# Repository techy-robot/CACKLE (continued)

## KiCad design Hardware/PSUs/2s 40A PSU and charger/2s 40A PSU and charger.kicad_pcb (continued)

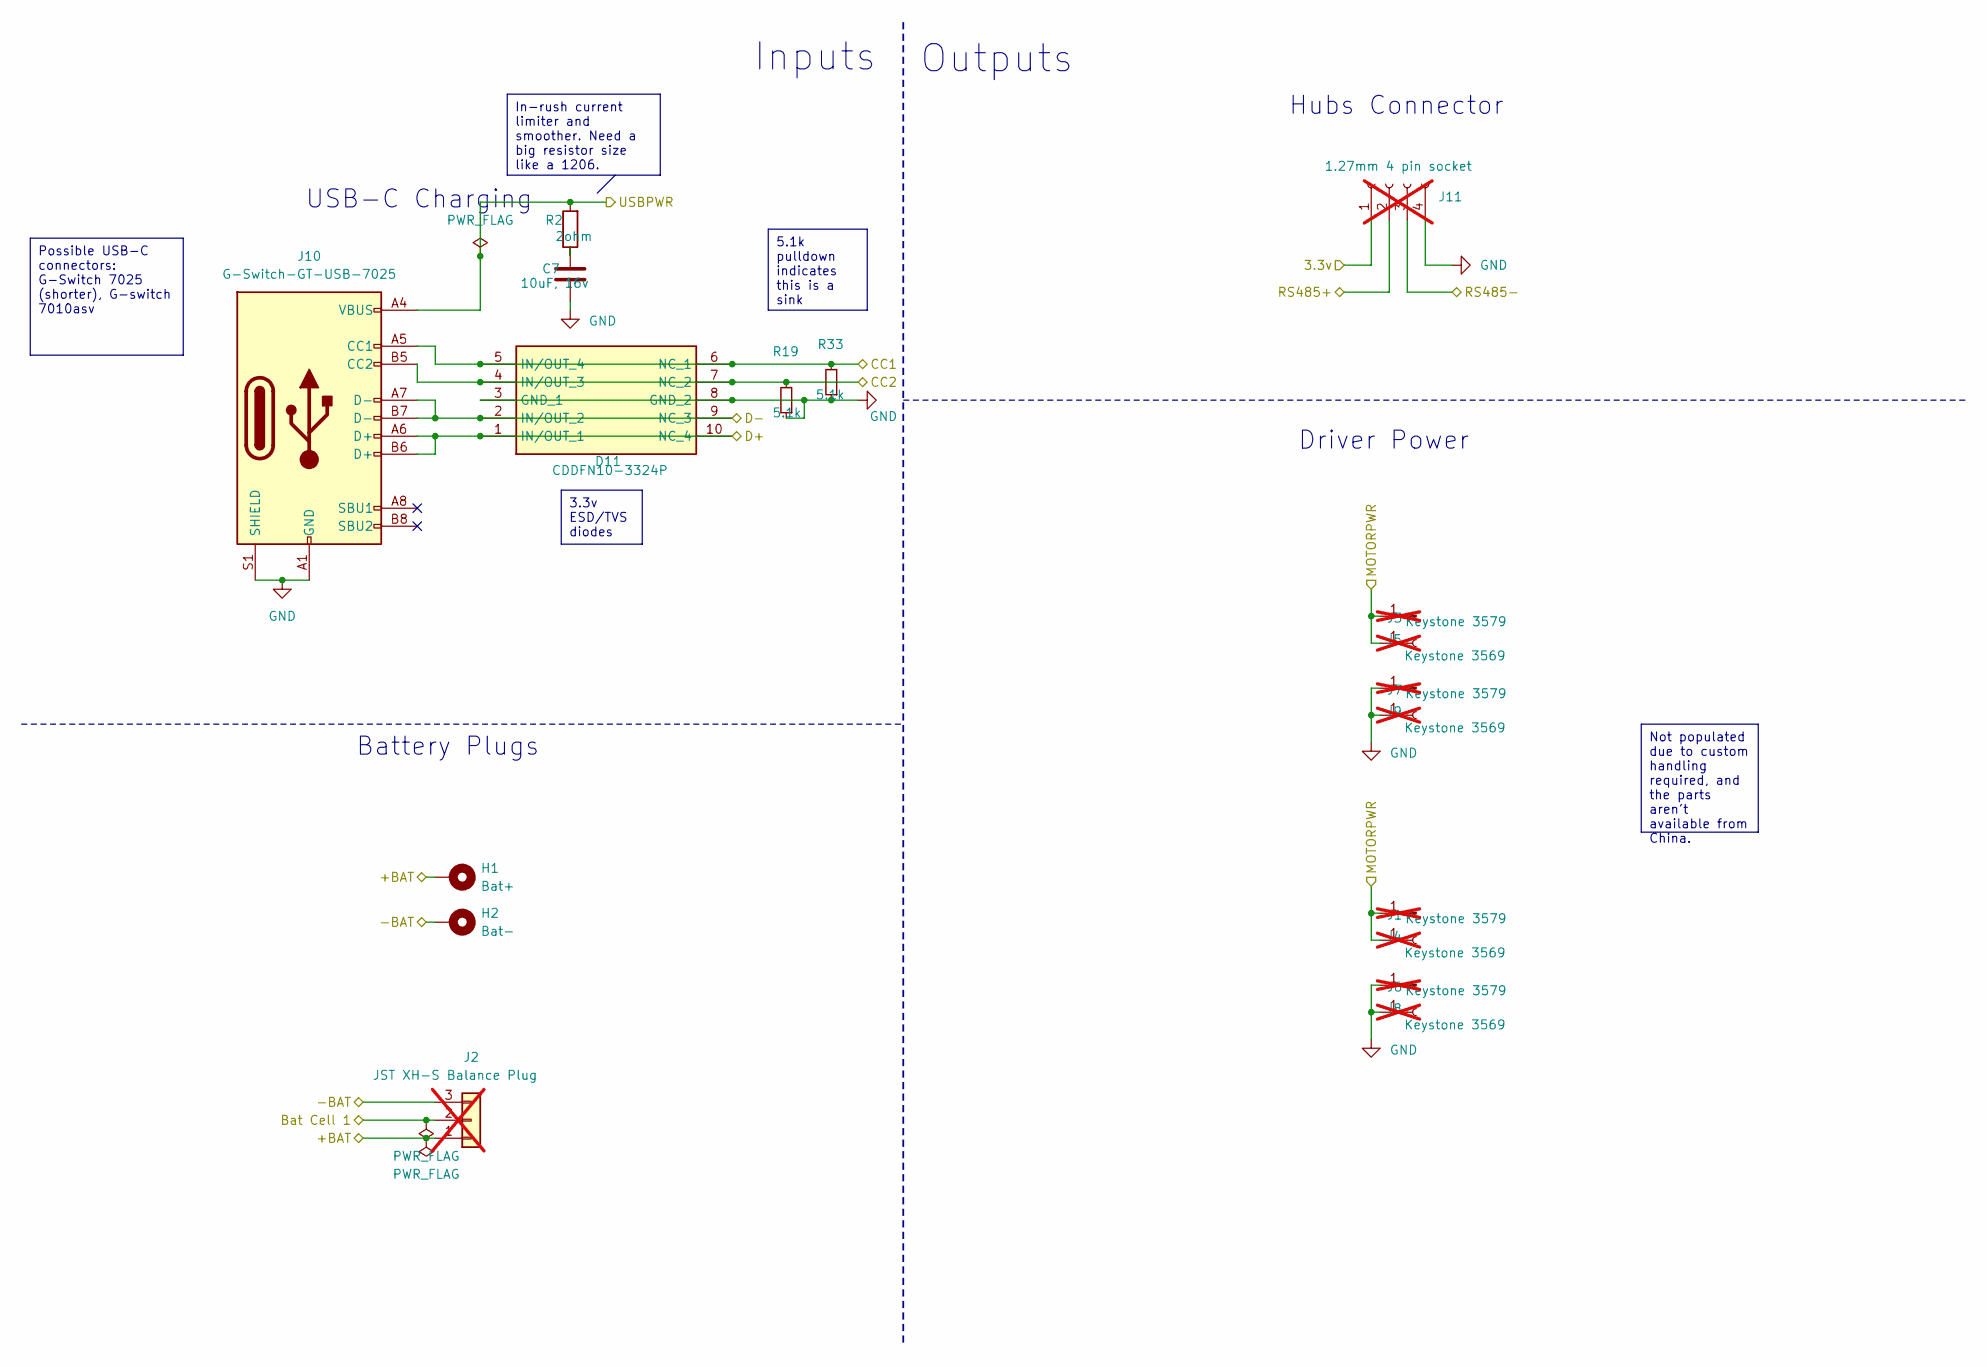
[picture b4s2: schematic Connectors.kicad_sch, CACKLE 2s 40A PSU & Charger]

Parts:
C7: 10uF, 16v; C_0805_2012Metric; LCSC C15850
D11: CDDFN10-3324P; CDDFN103324P; Mouser Part Number 652-CDDFN10-3324P
H1: Bat+; MountingHole_2.2mm_M2_Pad_Via
H2: Bat-; MountingHole_2.2mm_M2_Pad_Via
J1, J3, J6, J7: Keystone 3579; Keystone_3579; not fitted
J2: JST XH-S Balance Plug; JST_XH_S3B-XH-A_1x03_P2.50mm_Horizontal; LCSC C161860; not fitted
J4, J5, J8, J9: Keystone 3569; Keystone_3569_half; not fitted
J10: G-Switch-GT-USB-7025; USB_C_G-Switch_GT-USB-7025-JLCPCBv; LCSC C963213
J11: 1.27mm 4 pin socket; PinSocket_1x04_P1.27mm_Vertical; not fitted
R2: 2ohm; R_0805_2012Metric; LCSC C17521
R19, R33: 5.1k; R_0402_1005Metric; LCSC C25905

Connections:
/Battery Balancer/+BAT: H1.1, J2.1; also elsewhere on the board
/Battery Balancer/-BAT: H2.1, J2.3; also elsewhere on the board
/Battery Balancer/Bat Cell 1: J2.2; also elsewhere on the board
/Battery Charger/IN: J10.A4 (VBUS), J10.A9 (VBUS), J10.B4 (VBUS), J10.B9 (VBUS), R2.2; also elsewhere on the board
/Battery Charger/MOTORPWR: J1.1, J3.1, J4.1, J5.1; also elsewhere on the board
/Connectors/3.3v: J11.1; also elsewhere on the board
/Connectors/CC1: D11.5 (IN/OUT_4), D11.6 (NC_1), J10.A5 (CC1), R33.2; also elsewhere on the board
/Connectors/CC2: D11.4 (IN/OUT_3), D11.7 (NC_2), J10.B5 (CC2), R19.2; also elsewhere on the board
/Connectors/D+: D11.1 (IN/OUT_1), D11.10 (NC_4), J10.A6 (D+), J10.B6 (D+); also elsewhere on the board
/Connectors/D-: D11.2 (IN/OUT_2), D11.9 (NC_3), J10.A7 (D-), J10.B7 (D-); also elsewhere on the board
/Connectors/RS485+: J11.2; also elsewhere on the board
/Connectors/RS485-: J11.3; also elsewhere on the board
GND: C7.2, D11.3 (GND_1), D11.8 (GND_2), J6.1, J7.1, J8.1, J9.1, J10.A1 (GND), J10.A12 (GND), J10.B1 (GND), J10.B12 (GND), J10.GND, J10.S1 (SHIELD), J11.4, R19.1, R33.1; also elsewhere on the board
unnamed: C7.1, R2.1

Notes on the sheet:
In-rush current limiter and smoother. Need a big resistor size like a 1206.
5.1k pulldown indicates this is a sink
Possible USB-C connectors: G-Switch 7025 (shorter), G-switch 7010asv
3.3v ESD/TVS diodes
Not populated due to custom handling required, and the parts aren't available from China.
Outputs
USB-C Charging
Inputs
Driver Power
Hubs Connector
Battery Plugs

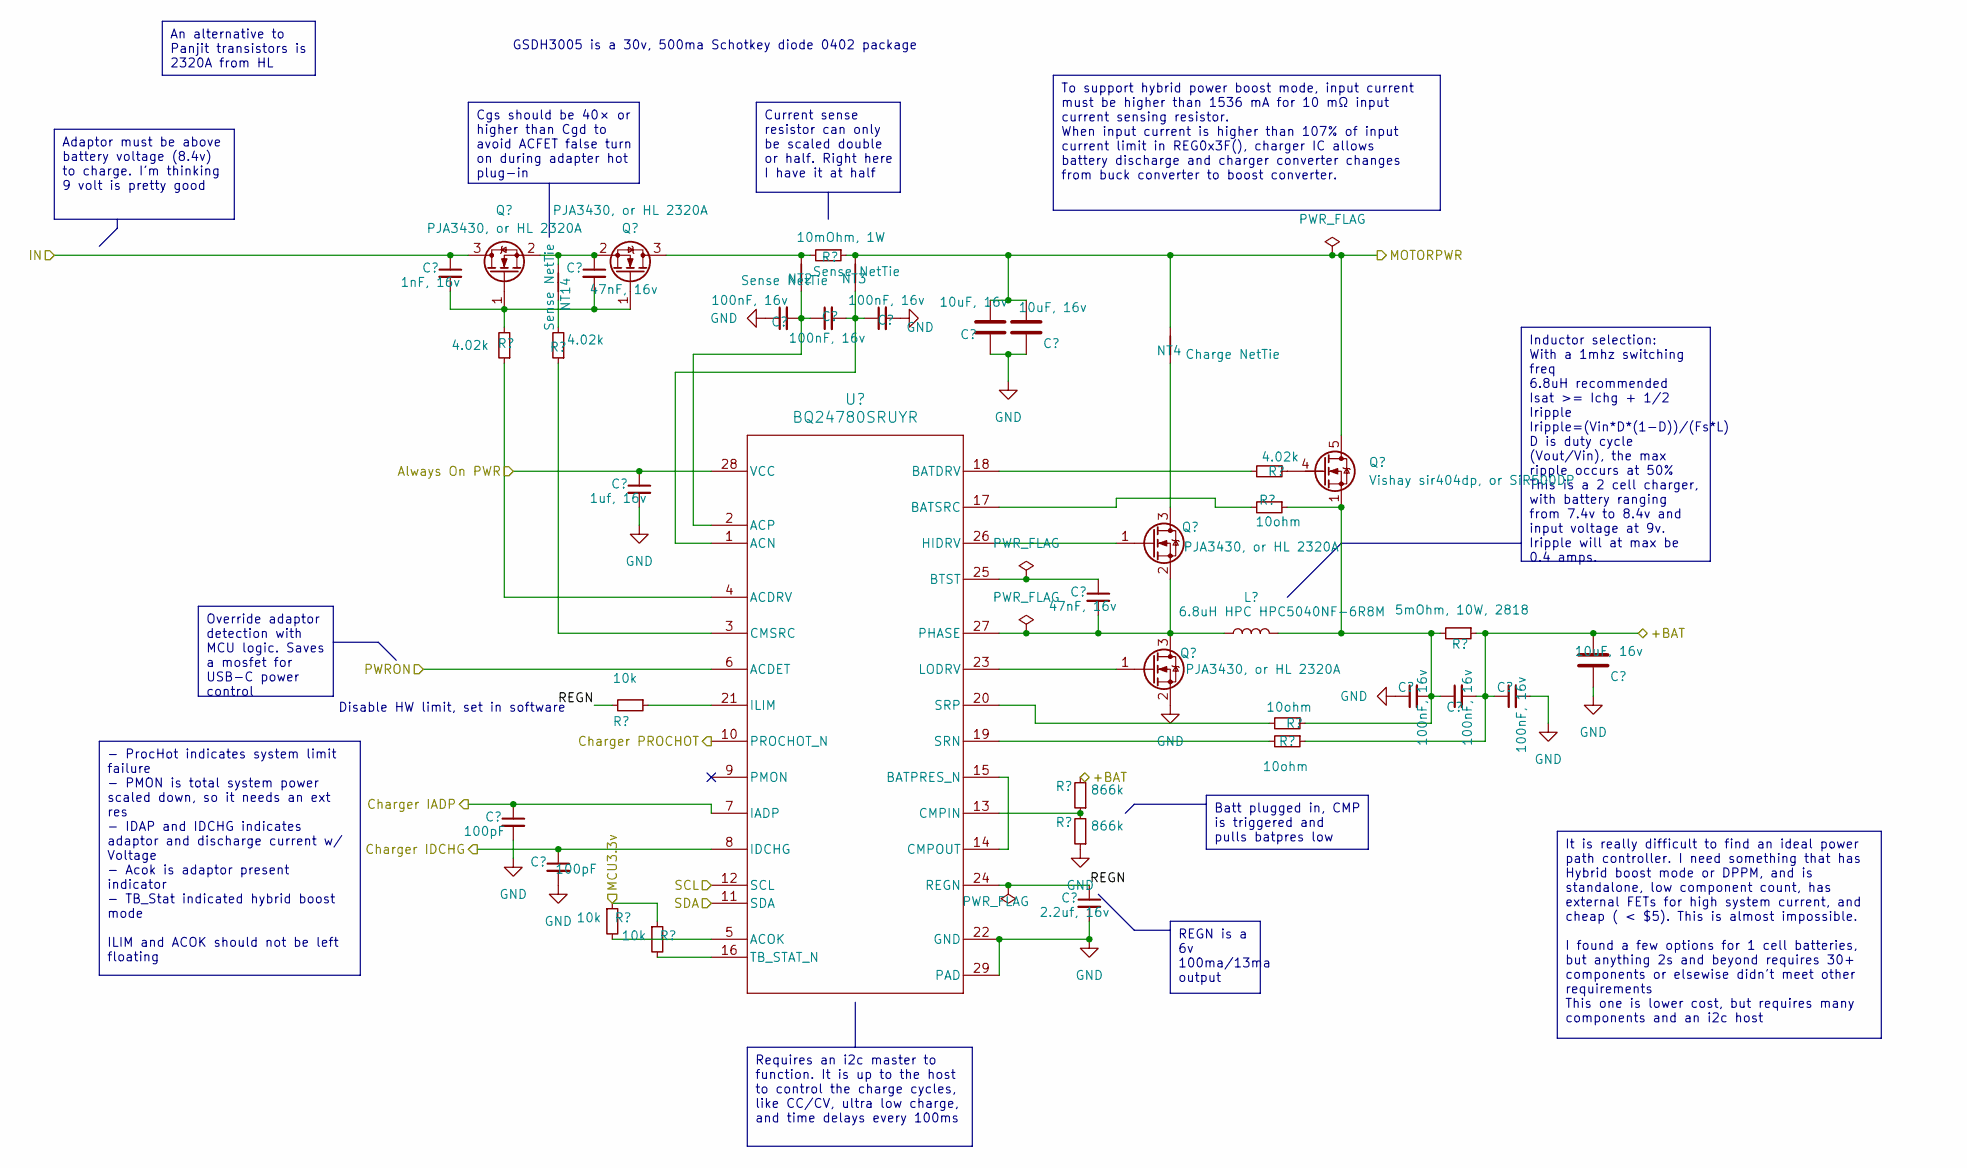
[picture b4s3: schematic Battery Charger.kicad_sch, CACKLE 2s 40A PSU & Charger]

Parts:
C5: 1nF, 16v; C_0402_1005Metric
C6, C17: 47nF, 16v; C_0603_1608Metric
C9, C10, C11, C21, C22, C23: 100nF, 16v; C_0402_1005Metric
C12, C14, C20: 10uF, 16v; C_0805_2012Metric
C15: 1uf, 16v; C_0402_1005Metric
C24: 2.2uf, 16v; C_0603_1608Metric
C29, C30: 100pF; C_0402_1005Metric
L2: 6.8uH HPC HPC5040NF-6R8M; L_Bourns_SDR0604
NT2, NT3, NT14: Sense NetTie; NetTie-2_SMD_Pad0.2mm
NT4: Charge NetTie; NetTie-2_SMD_Pad0.8mm
Q1, Q2, Q4, Q5: PJA3430, or HL 2320A; SC-59
Q3: Vishay sir404dp, or SiR500DP; PQFN-8-EP_6x5mm_P1.27mm_Generic; LCSC C3289487
R1: 10mOhm, 1W; R_1206_3216Metric
R7, R8, R10: 4.02k; R_0402_1005Metric
R12, R21, R22: 10ohm; R_0402_1005Metric
R18: 5mOhm, 10W, 2818; R_Vishay_2818
R20, R23, R24: 10k; R_0402_1005Metric
R30, R31: 866k; R_0402_1005Metric
U3: BQ24780SRUYR; RUY0028A

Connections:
/Battery Balancer/+BAT: C20.2, C22.2, C23.1, R18.1, R22.1, R30.2; also elsewhere on the board
/Battery Charger/Always On PWR: C15.1, U3.28 (VCC); also elsewhere on the board
/Battery Charger/Charger IADP: C29.1, U3.7 (IADP); also elsewhere on the board
/Battery Charger/Charger IDCHG: C30.1, U3.8 (IDCHG); also elsewhere on the board
/Battery Charger/Charger PROCHOT: U3.10 (PROCHOT_N); also elsewhere on the board
/Battery Charger/IN: C5.1, Q1.3 (D); also elsewhere on the board
/Battery Charger/MCU3.3v: R23.1, R24.1; also elsewhere on the board
/Battery Charger/MOTORPWR: C12.2, C14.2, NT3.2, NT4.2, Q3.5 (D), Q3.6 (D), Q3.7 (D), Q3.8 (D), R1.1; also elsewhere on the board
/Battery Charger/PWRON: U3.6 (ACDET); also elsewhere on the board
/Battery Charger/REGN: C24.1, R20.2, U3.24 (REGN)
/SCL: U3.12 (SCL); also elsewhere on the board
/SDA: U3.11 (SDA); also elsewhere on the board
GND: C9.1, C11.2, C12.1, C14.1, C15.2, C20.1, C21.1, C23.2, C24.2, C29.2, C30.2, Q5.2 (S), R31.1, U3.22 (GND), U3.29 (PAD); also elsewhere on the board
unnamed: C21.2, C22.1, L2.2, Q3.1 (S), Q3.2 (S), Q3.3 (S), R12.1, R18.2, R21.1
unnamed: NT14.1, R7.2
unnamed: C5.2, C6.2, Q1.1 (G), Q2.1 (G), R8.2
unnamed: C6.1, NT14.2, Q1.2 (S), Q2.2 (S)
unnamed: NT2.2, Q2.3 (D), R1.2
unnamed: Q3.4 (G), R10.1
unnamed: NT4.1, Q4.3 (D)
unnamed: Q4.1 (G), U3.26 (HIDRV)
unnamed: C17.2, L2.1, Q4.2 (S), Q5.3 (D), U3.27 (PHASE)
unnamed: Q5.1 (G), U3.23 (LODRV)
unnamed: R8.1, U3.4 (ACDRV)
unnamed: C10.2, C11.1, NT3.1, U3.1 (ACN)
unnamed: R23.2, U3.5 (ACOK)
unnamed: C9.2, C10.1, NT2.1, U3.2 (ACP)
unnamed: R10.2, U3.18 (BATDRV)
unnamed: U3.14 (CMPOUT), U3.15 (BATPRES_N)
unnamed: R12.2, U3.17 (BATSRC)
unnamed: C17.1, U3.25 (BTST)
unnamed: R30.1, R31.2, U3.13 (CMPIN)
unnamed: R7.1, U3.3 (CMSRC)
unnamed: R20.1, U3.21 (ILIM)
unnamed: R22.2, U3.19 (SRN)
unnamed: R21.2, U3.20 (SRP)
unnamed: R24.2, U3.16 (TB_STAT_N)

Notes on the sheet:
To support hybrid power boost mode, input current must be higher than 1536 mA for 10 mΩ input current sensing resistor. When input current is higher than 107% of input current limit in REG0x3F(), charger IC allows battery discharge and charger converter changes from buck converter to boost converte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
Batt plugged in, CMP is triggered and pulls batpres low
Inductor selection: With a 1mhz switching freq 6.8uH recommended Isat >= Ichg + 1/2 Iripple Iripple=(Vin*D*(1-D))/(Fs*L) D is duty cycle (Vout/Vin), the max ripple occurs at 50% This is a 2 cell charger, with battery ranging from 7.4v to 8.4v and input voltage at 9v. Iripple will at max be 0.4 amps.
It is really difficult to find an ideal power path controller. I need something that has Hybrid boost mode or DPPM, and is standalone, low component count, has external FETs for high system current, and cheap ( < $5). This is almost impossible. I found a few options for 1 cell batteries, but anythi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
Requires an i2c master to function. It is up to the host to control the charge cycles, like CC/CV, ultra low charge, and time delays every 100ms
Cgs should be 40× or higher than Cgd to avoid ACFET false turn on during adapter hot plug-in
Current sense resistor can only be scaled double or half. Right here I have it at half
Override adaptor detection with MCU logic. Saves a mosfet for USB-C power control
Adaptor must be above battery voltage (8.4v) to charge. I'm thinking 9 volt is pretty good
REGN is a 6v 100ma/13ma output
An alternative to Panjit transistors is 2320A from HL
- ProcHot indicates system limit failure - PMON is total system power scaled down, so it needs an ext res - IDAP and IDCHG indicates adaptor and discharge current w/ Voltage - Acok is adaptor present indicator - TB_Stat indicated hybrid boost mode ILIM and ACOK should not be left floating
GSDH3005 is a 30v, 500ma Schotkey diode 0402 package
Disable HW limit, set in software

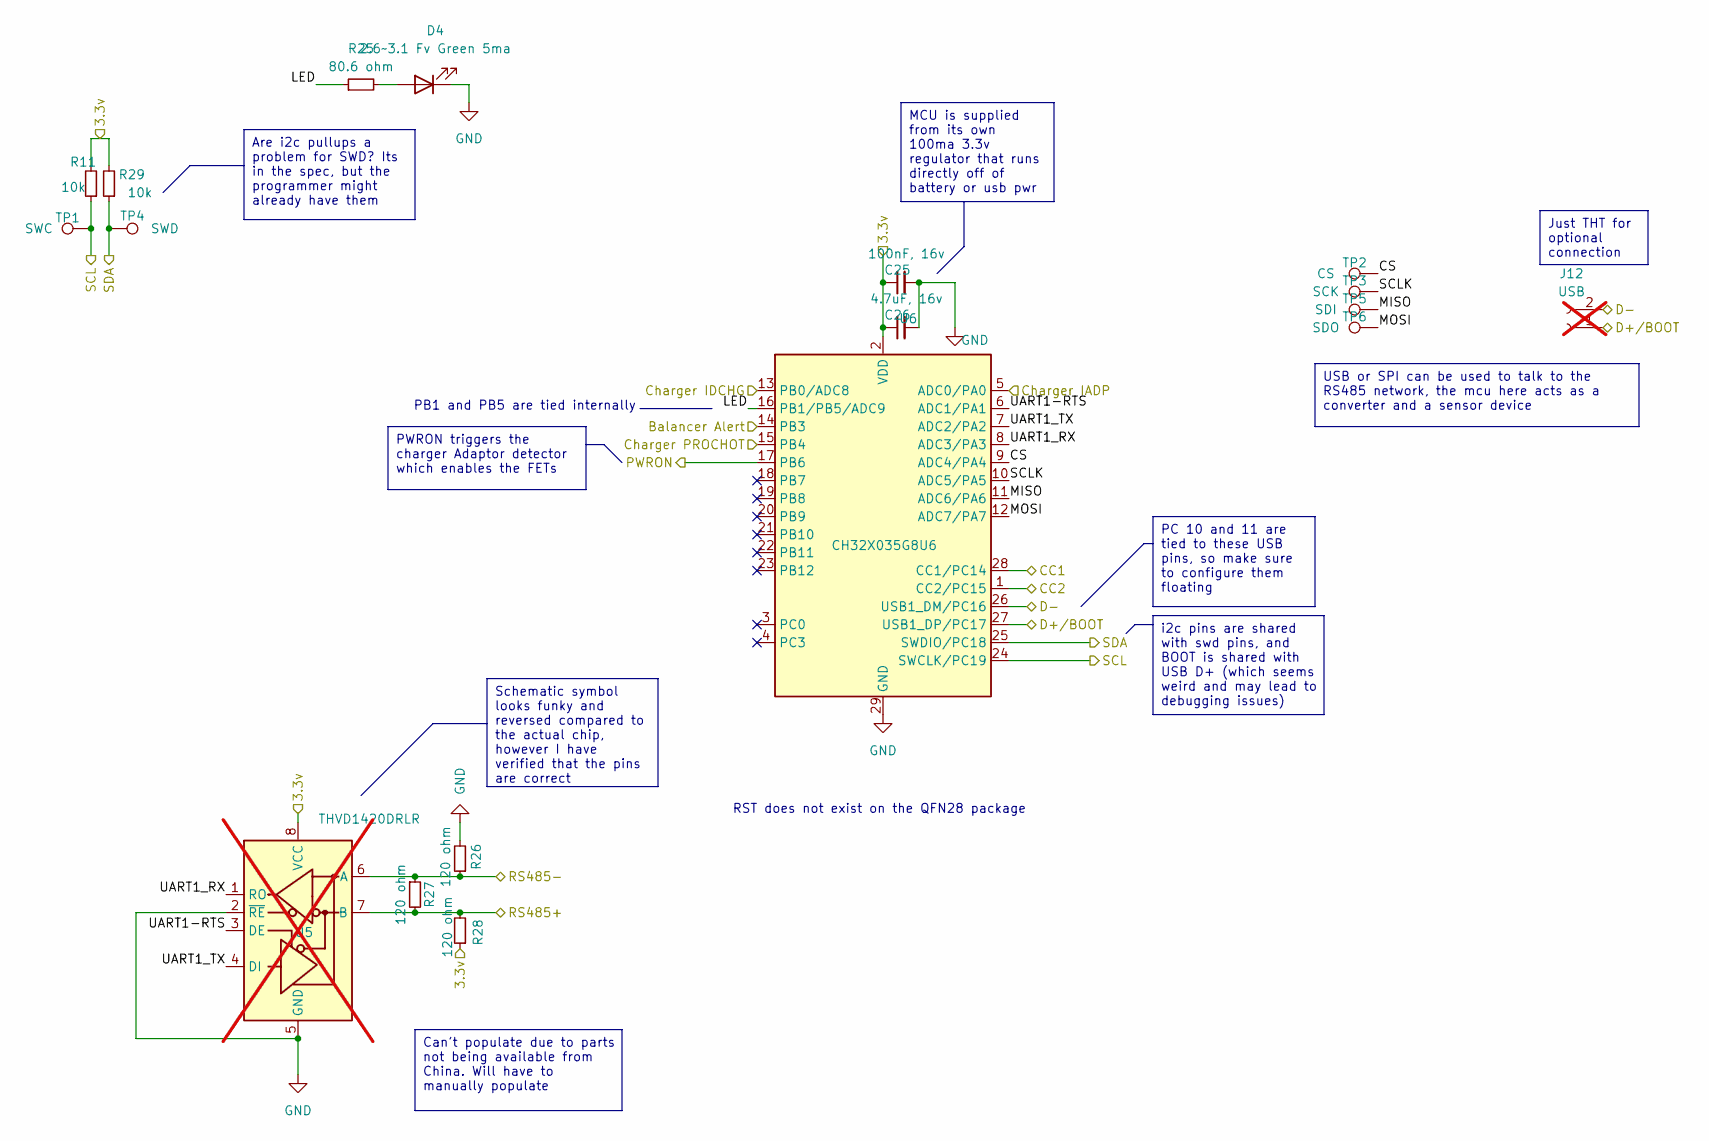
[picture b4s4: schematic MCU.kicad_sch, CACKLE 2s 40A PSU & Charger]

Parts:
C25: 100nF, 16v; C_0402_1005Metric; LCSC C1525
C26: 4.7uF, 16v; C_0603_1608Metric; LCSC C19666
D4: 2.6~3.1 Fv Green 5ma; LED_0603_1608Metric_Pad1.05x0.95mm_HandSolder; LCSC C3028858
J12: USB; PinHeader_1x02_P1.27mm_Vertical; not fitted
R11, R29: 10k; R_0402_1005Metric; LCSC C25744
R25: 80.6 ohm; R_0402_1005Metric; LCSC C185392
R26, R27, R28: 120 ohm; R_0402_1005Metric; LCSC C25079
TP1: SWC; TestPoint_Pad_D1.0mm
TP2: CS; TestPoint_Pad_D1.0mm
TP3: SCK; TestPoint_Pad_D1.0mm
TP4: SWD; TestPoint_Pad_D1.0mm
TP5: SDI; TestPoint_Pad_D1.0mm
TP6: SDO; TestPoint_Pad_D1.0mm
U5: THVD1420DRLR; SOT-583-8; not fitted
U6: CH32X035G8U6; QFN-28-1EP_4x4mm_P0.4mm_EP2.8x2.8mm; LCSC C7437027

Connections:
/Battery Balancer/Balancer Alert: U6.14 (PB3); also elsewhere on the board
/Battery Charger/Charger IADP: U6.5 (ADC0/PA0); also elsewhere on the board
/Battery Charger/Charger IDCHG: U6.13 (PB0/ADC8); also elsewhere on the board
/Battery Charger/Charger PROCHOT: U6.15 (PB4); also elsewhere on the board
/Battery Charger/MCU3.3v: C25.1, C26.1, R11.2, R28.1, R29.2, U5.8 (VCC), U6.2 (VDD); also elsewhere on the board
/Battery Charger/PWRON: U6.17 (PB6); also elsewhere on the board
/Connectors/CC1: U6.28 (CC1/PC14); also elsewhere on the board
/Connectors/CC2: U6.1 (CC2/PC15); also elsewhere on the board
/Connectors/D+: J12.1, U6.27 (USB1_DP/PC17); also elsewhere on the board
/Connectors/D-: J12.2, U6.26 (USB1_DM/PC16); also elsewhere on the board
/Connectors/RS485+: R27.2, R28.2, U5.7 (B); also elsewhere on the board
/Connectors/RS485-: R26.1, R27.1, U5.6 (A); also elsewhere on the board
/MCU/CS: TP2.1, U6.9 (ADC4/PA4)
/MCU/LED: R25.1, U6.16 (PB1/PB5/ADC9)
/MCU/MISO: TP5.1, U6.11 (ADC6/PA6)
/MCU/MOSI: TP6.1, U6.12 (ADC7/PA7)
/MCU/SCLK: TP3.1, U6.10 (ADC5/PA5)
/MCU/UART1-RTS: U5.3 (DE), U6.6 (ADC1/PA1)
/MCU/UART1_RX: U5.1 (RO), U6.8 (ADC3/PA3)
/MCU/UART1_TX: U5.4 (DI), U6.7 (ADC2/PA2)
/SCL: R11.1, TP1.1, U6.24 (SWCLK/PC19); also elsewhere on the board
/SDA: R29.1, TP4.1, U6.25 (SWDIO/PC18); also elsewhere on the board
GND: C25.2, C26.2, D4.1 (K), R26.2, U5.2 (~RE), U5.5 (GND), U6.29 (GND); also elsewhere on the board
unnamed: D4.2 (A), R25.2

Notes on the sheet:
i2c pins are shared with swd pins, and BOOT is shared with USB D+ (which seems weird and may lead to debugging issues)
MCU is supplied from its own 100ma 3.3v regulator that runs directly off of battery or usb pwr
USB or SPI can be used to talk to the RS485 network, the mcu here acts as a converter and a sensor device
Just THT for optional connection
PC 10 and 11 are tied to these USB pins, so make sure to configure them floating
PWRON triggers the charger Adaptor detector which enables the FETs
Can't populate due to parts not being available from China. Will have to manually populate
Schematic symbol looks funky and reversed compared to the actual chip, however I have verified that the pins are correct
Are i2c pullups a problem for SWD? Its in the spec, but the programmer might already have them
RST does not exist on the QFN28 package
PB1 and PB5 are tied internally

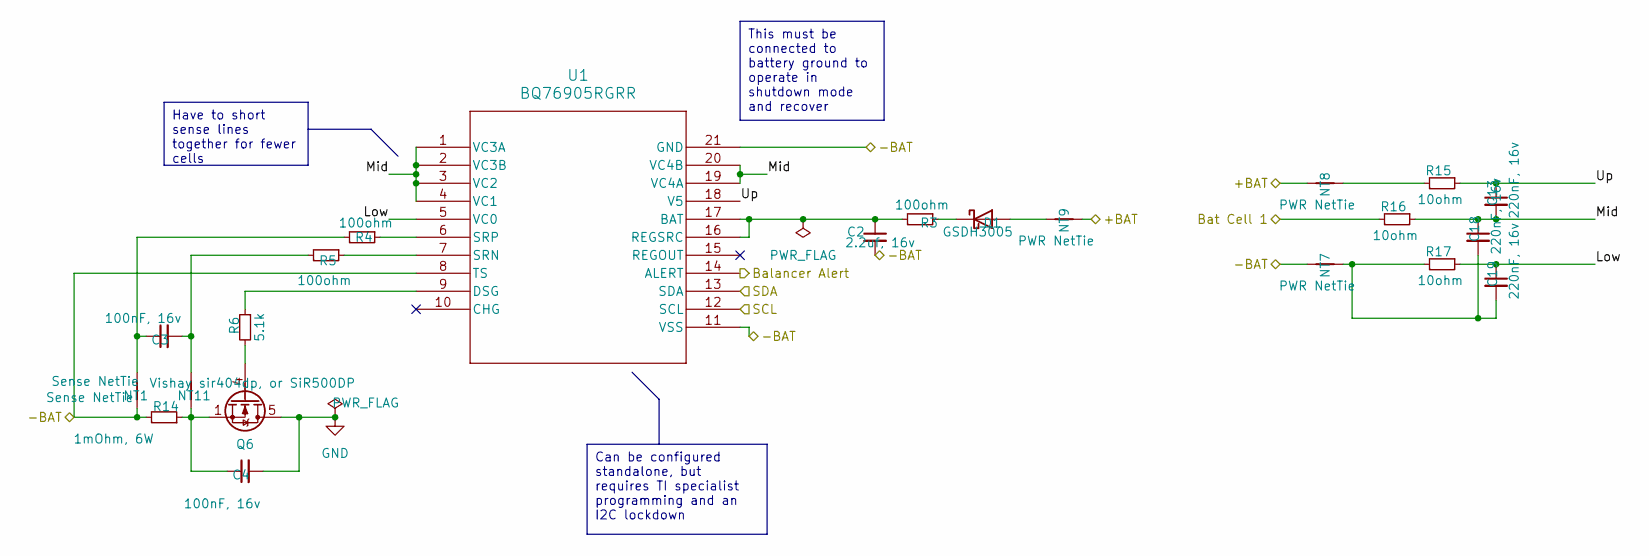
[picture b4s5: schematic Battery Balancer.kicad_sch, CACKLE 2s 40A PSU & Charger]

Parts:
C2: 2.2uf, 16v; C_0603_1608Metric; LCSC C23630
C3, C4: 100nF, 16v; C_0402_1005Metric; LCSC C1525
C13, C18, C19: 220nF, 16v; C_0402_1005Metric; LCSC C16772
D1: GSDH3005; D_0402_1005Metric; LCSC C2837790
NT1, NT11: Sense NetTie; NetTie-2_SMD_Pad0.2mm
NT7, NT8, NT9: PWR NetTie; NetTie-2_SMD_Pad0.28mm
Q6: Vishay sir404dp, or SiR500DP; PQFN-8-EP_6x5mm_P1.27mm_Generic; LCSC C3289487
R3, R4, R5: 100ohm; R_0402_1005Metric; LCSC C25076
R6: 5.1k; R_0402_1005Metric; LCSC C25905
R14: 1mOhm, 6W; R_2512_6332Metric_6W; LCSC C19270875
R15, R16, R17: 10ohm; R_0402_1005Metric; LCSC C25077
U1: BQ76905RGRR; VQFN20_RGR_TEX; LCSC C22394458

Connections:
/Battery Balancer/+BAT: NT8.2, NT9.1; also elsewhere on the board
/Battery Balancer/-BAT: C2.2, NT1.1, NT7.2, R14.2, U1.8 (TS), U1.11 (VSS), U1.21 (GND); also elsewhere on the board
/Battery Balancer/Balancer Alert: U1.14 (ALERT); also elsewhere on the board
/Battery Balancer/Bat Cell 1: R16.2; also elsewhere on the board
/Battery Balancer/Low: C19.1, R17.1, U1.5 (VC0)
/Battery Balancer/Mid: C13.2, C18.1, R16.1, U1.1 (VC3A), U1.2 (VC3B), U1.3 (VC2), U1.4 (VC1), U1.19 (VC4A), U1.20 (VC4B)
/Battery Balancer/Up: C13.1, R15.1, U1.18 (V5)
/SCL: U1.12 (SCL); also elsewhere on the board
/SDA: U1.13 (SDA); also elsewhere on the board
GND: C4.2, Q6.5 (D), Q6.6 (D), Q6.7 (D), Q6.8 (D); also elsewhere on the board
unnamed: C3.1, NT1.2, R4.2
unnamed: C3.2, NT11.2, R5.2
unnamed: C4.1, NT11.1, Q6.1 (S), Q6.2 (S), Q6.3 (S), R14.1
unnamed: C18.2, C19.2, NT7.1, R17.2
unnamed: D1.2 (A), NT9.2
unnamed: D1.1 (K), R3.1
unnamed: NT8.1, R15.2
unnamed: Q6.4 (G), R6.2
unnamed: C2.1, R3.2, U1.16 (REGSRC), U1.17 (BAT)
unnamed: R6.1, U1.9 (DSG)
unnamed: R5.1, U1.7 (SRN)
unnamed: R4.1, U1.6 (SRP)

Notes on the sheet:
This must be connected to battery ground to operate in shutdown mode and recover
Can be configured standalone, but requires TI specialist programming and an I2C lockdown
Have to short sense lines together for fewer cells

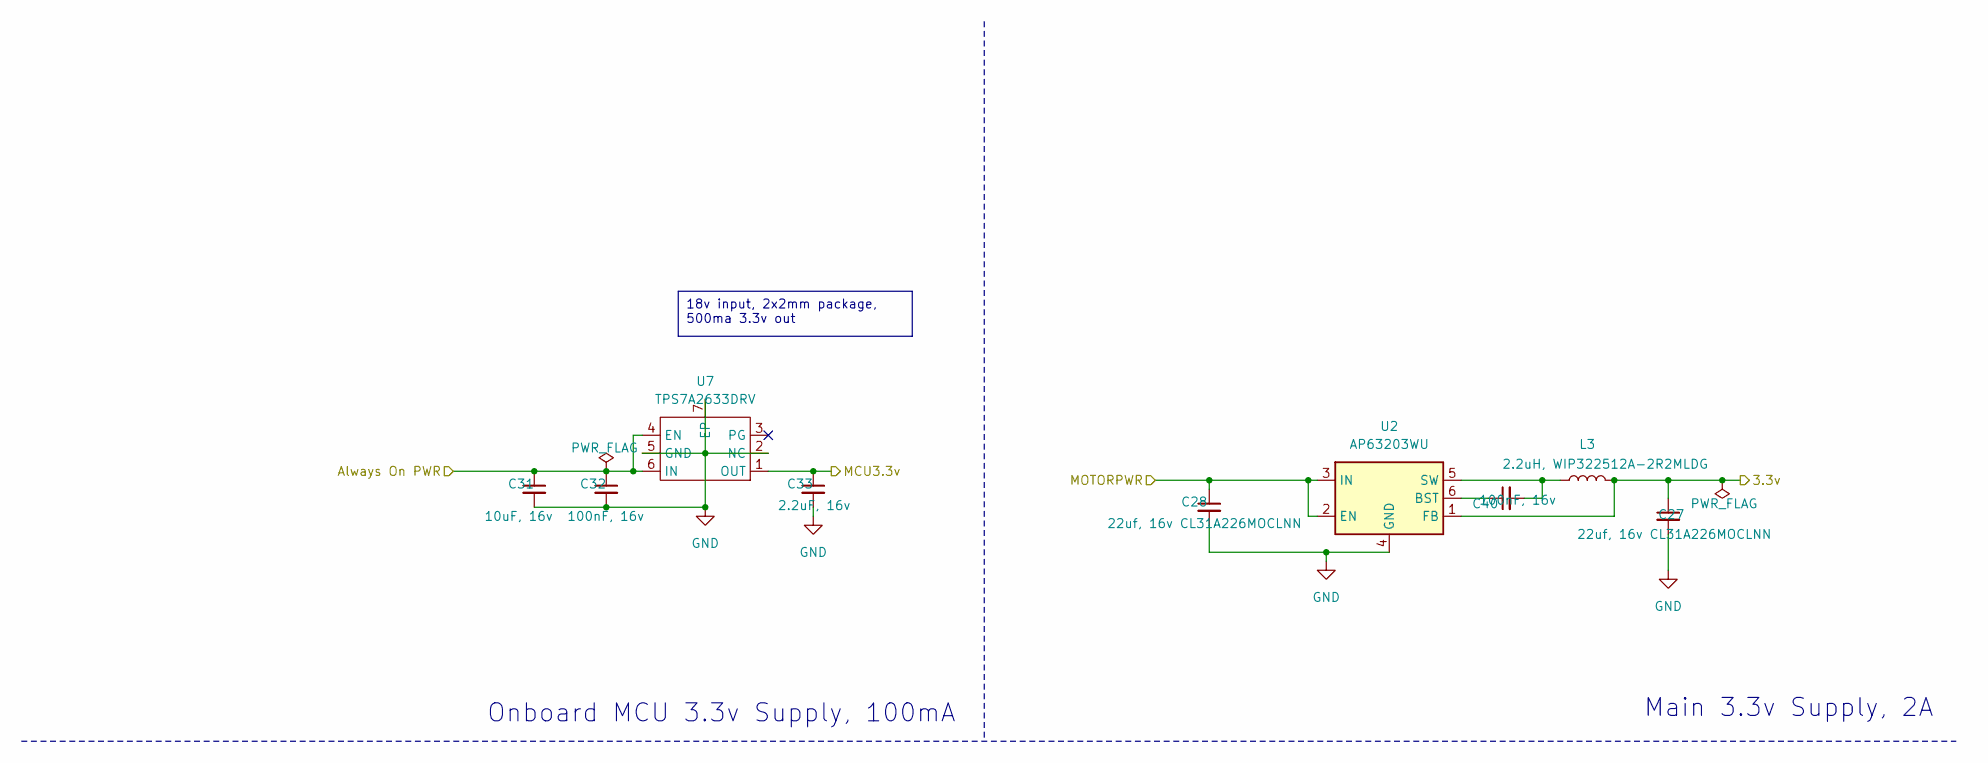
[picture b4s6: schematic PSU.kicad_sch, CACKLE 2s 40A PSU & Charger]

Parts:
C27, C28: 22uf, 16v CL31A226MOCLNN; C_1206_3216Metric; LCSC C159758
C31: 10uF, 16v; C_0603_1608Metric; LCSC C96446
C32: 100nF, 16v; C_0402_1005Metric; LCSC C1525
C33: 2.2uF, 16v; C_0402_1005Metric; LCSC C12530
C40: 100nF, 16v; C_0603_1608Metric; LCSC C14663
L3: 2.2uH, WIP322512A-2R2MLDG; L_1008_2520Metric; LCSC C5832372
U2: AP63203WU; TSOT-23-6; LCSC C780769
U7: TPS7A2633DRV; WSON-6-1EP_2x2mm_P0.65mm_EP1x1.6mm; LCSC C2876256

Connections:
/Battery Charger/Always On PWR: C31.1, C32.1, U7.4 (EN), U7.6 (IN); also elsewhere on the board
/Battery Charger/MCU3.3v: C33.1, U7.1 (OUT); also elsewhere on the board
/Battery Charger/MOTORPWR: C28.1, U2.2 (EN), U2.3 (IN); also elsewhere on the board
/Connectors/3.3v: C27.1, L3.2, U2.1 (FB); also elsewhere on the board
GND: C27.2, C28.2, C31.2, C32.2, C33.2, U2.4 (GND), U7.2 (NC), U7.5 (GND), U7.7 (EP); also elsewhere on the board
unnamed: C40.1, U2.6 (BST)
unnamed: C40.2, L3.1, U2.5 (SW)

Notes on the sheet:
18v input, 2x2mm package, 500ma 3.3v out
Onboard MCU 3.3v Supply, 100mA
Main 3.3v Supply, 2A

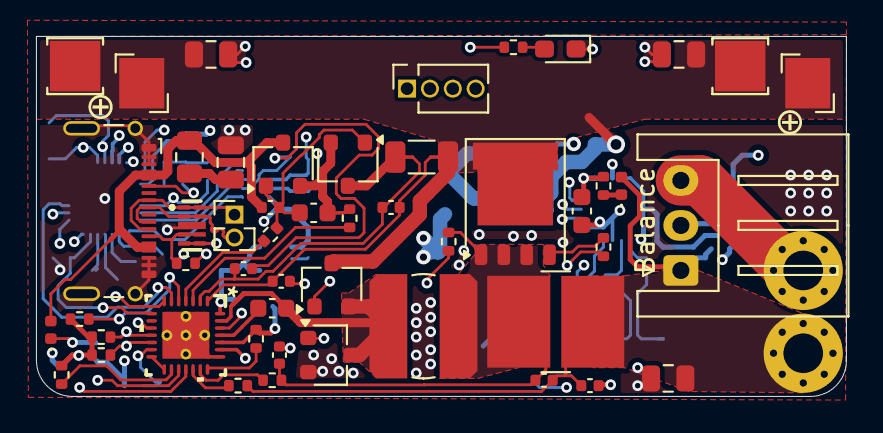
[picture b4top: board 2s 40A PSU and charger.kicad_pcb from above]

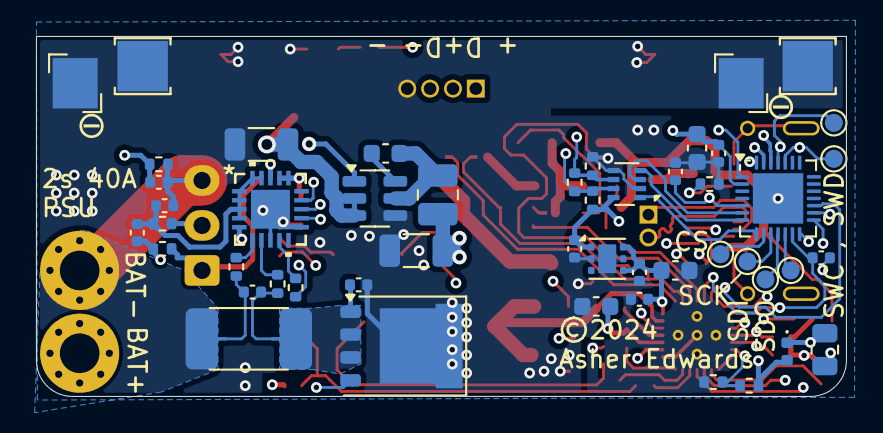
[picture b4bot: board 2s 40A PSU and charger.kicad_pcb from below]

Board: 4 copper layers, 45.0 x 20.0 mm, 112 parts (55 on the bottom side), 77 nets.

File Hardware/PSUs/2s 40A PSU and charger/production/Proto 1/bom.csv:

Designator,Footprint,Quantity,Value,LCSC Part #
"C10, C11, C21, C22, C23, C25, C3, C32, C4, C9",0402,10,"100nF, 16v",C1525
"C12, C14, C20, C7",0805,4,"10uF, 16v",C15850
"C13, C18, C19",0402,3,"220nF, 16v",C16772
C15,0402,1,"1uf, 16v",C52923
"C17, C6",0603,2,"47nF, 16v",C1622
"C2, C24",0603,2,"2.2uf, 16v",C23630
C26,0603,1,"4.7uF, 16v",C19666
"C27, C28",1206,2,"22uf, 16v CL31A226MOCLNN",C159758
"C29, C30",0402,2,100pF,C1546
C31,0603,1,"10uF, 16v",C96446
C33,0402,1,"2.2uF, 16v",C12530
C40,0603,1,"100nF, 16v",C14663
C5,0402,1,"1nF, 16v",C1523
"D1, D2, D3",0402,3,GSDH3005,C2837790
D11,CDDFN103324P,1,CDDFN10-3324P,C913227
D4,0603,1,2.6~3.1 Fv Green 5ma,C3028858
J10,USB_C_G-Switch_GT-USB-7025-JLCPCBv,1,G-Switch-GT-USB-7025,C963213
L2,L_Bourns_SDR0604,1,6.8uH HPC HPC5040NF-6R8M,C357072
L3,1008,1,"2.2uH, WIP322512A-2R2MLDG",C5832372
"Q1, Q2, Q4, Q5",SC-59,4,"PJA3430, or HL 2320A",C7437078
"Q3, Q6",PQFN-8-EP_6x5mm_P1.27mm_Generic,2,"Vishay sir404dp, or SiR500DP",C3289487
R1,1206,1,"10mOhm, 1W",C473031
"R10, R7, R8",0402,3,4.02k,C43251
"R11, R20, R23, R24, R29",0402,5,10k,C25744
"R12, R15, R16, R17, R21, R22",0402,6,10ohm,C25077
R14,2512,1,"1mOhm, 6W",C19270875
R18,R_Vishay_2818,1,"5mOhm, 10W, 2818",C2090564
"R19, R33, R6",0402,3,5.1k,C25905
R2,0805,1,2ohm,C17521
R25,0402,1,80.6 ohm,C185392
"R26, R27, R28",0402,3,120 ohm,C25079
"R3, R4, R5",0402,3,100ohm,C25076
"R30, R31",0402,2,866k,C137931
R9,0805,1,10ohm,C17415
U1,VQFN20_RGR_TEX,1,BQ76905RGRR,C22394458
U2,TSOT-23-6,1,AP63203WU,C780769
U3,RUY0028A,1,BQ24780SRUYR,
U6,QFN-28-1EP_4x4mm_P0.4mm_EP2.8x2.8mm,1,CH32X035G8U6,C7437027
U7,WSON-6-1EP_2x2mm_P0.65mm_EP1x1.6mm,1,TPS7A2633DRV,C2876256

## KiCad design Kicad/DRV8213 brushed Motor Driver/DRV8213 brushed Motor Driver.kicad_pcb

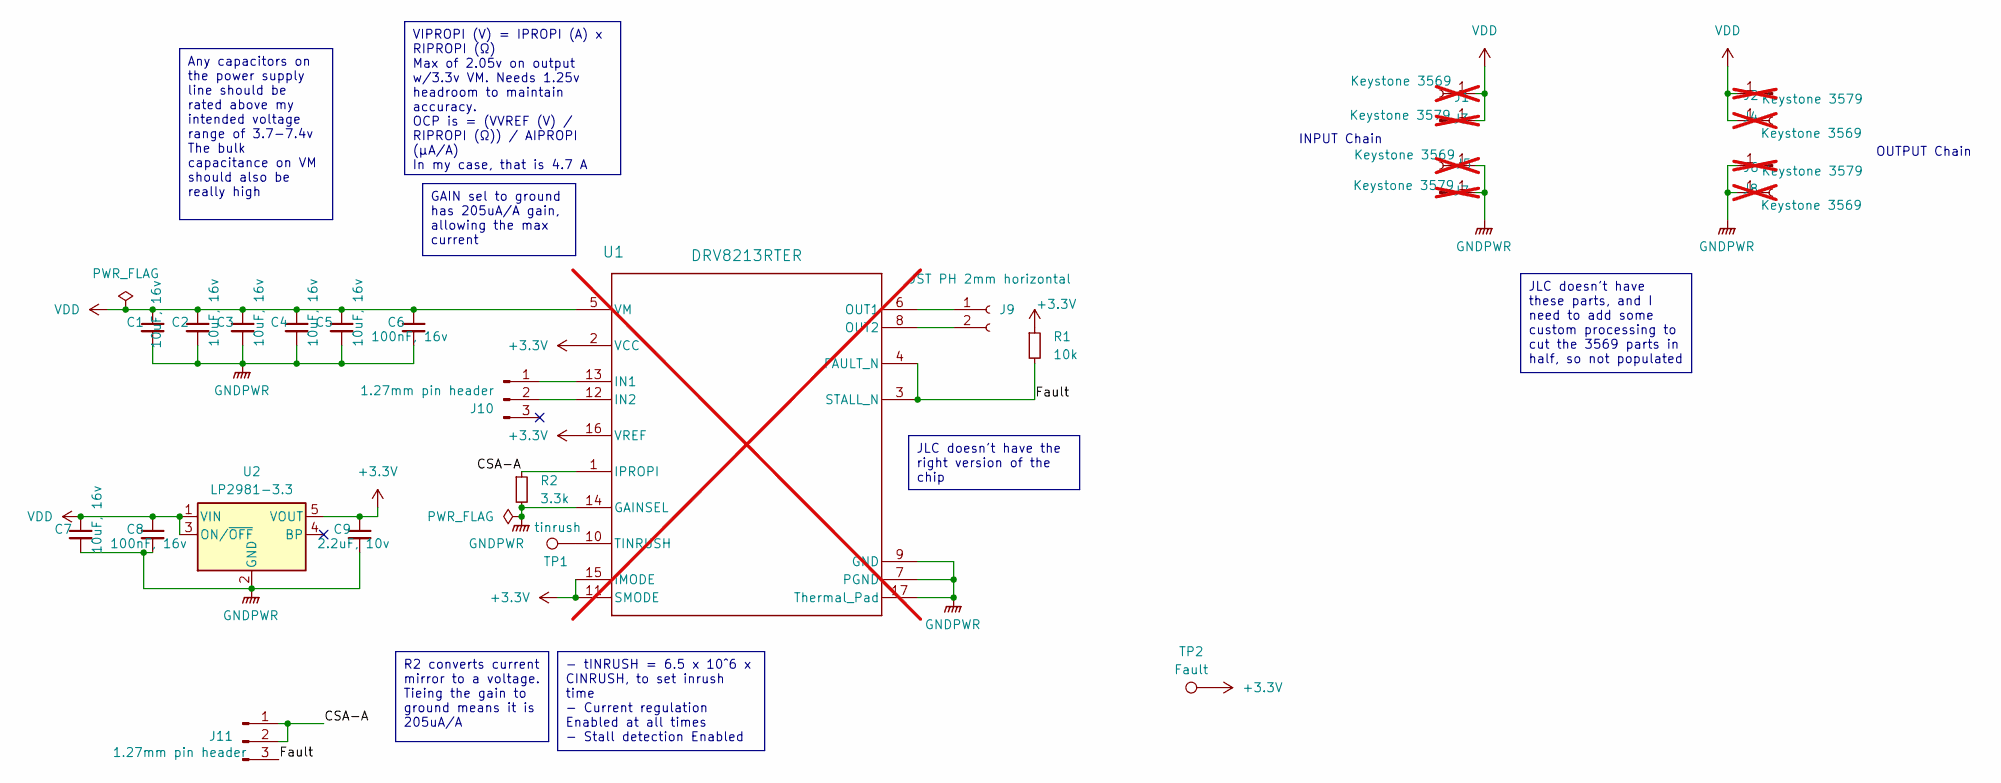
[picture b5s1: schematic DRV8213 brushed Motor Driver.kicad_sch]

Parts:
C1, C2, C3, C4, C5, C7: 10uF, 16v; C_0603_1608Metric; LCSC C96446
C6, C8: 100nF, 16v; C_0402_1005Metric; LCSC C1525
C9: 2.2uF, 10v; C_0402_1005Metric; LCSC C12530
J1, J4, J5, J8: Keystone 3569; Keystone_3569_half; not fitted
J2, J3, J6, J7: Keystone 3579; Keystone_3579; not fitted
J9: JST PH 2mm horizontal; JST_PH_S2B-PH-K_1x02_P2.00mm_Horizontal; LCSC C295747
J10, J11: 1.27mm pin header; PinHeader_1x03_P1.27mm_Horizontal
R1: 10k; R_0402_1005Metric; LCSC C25744
R2: 3.3k; R_0402_1005Metric; LCSC C25890
TP1: tinrush; TestPoint_Pad_D1.0mm
TP2: Fault; TestPoint_Pad_D1.0mm
U1: DRV8213RTER; WQFN-16-1EP_3x3mm_P0.5mm_EP1.68x1.68mm_ThermalVias; not fitted
U2: LP2981-3.3; SOT-23-5; LCSC C129997

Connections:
+3.3V: C9.1, R1.1, TP2.1, U1.2 (VCC), U1.11 (SMODE), U1.15 (IMODE), U1.16 (VREF), U2.5 (VOUT)
/CSA-A: J11.1, J11.2, R2.1, U1.1 (IPROPI)
/Fault: J11.3, R1.2, U1.3 (STALL_N), U1.4 (FAULT_N)
GNDPWR: C1.2, C2.2, C3.2, C4.2, C5.2, C6.2, C7.2, C8.2, C9.2, J5.1, J6.1, J7.1, J8.1, R2.2, U1.7 (PGND), U1.9 (GND), U1.14 (GAINSEL), U1.17 (Thermal_Pad), U2.2 (GND)
unnamed: J9.1, U1.6 (OUT1)
unnamed: J9.2, U1.8 (OUT2)
unnamed: J10.1, U1.13 (IN1)
unnamed: J10.2, U1.12 (IN2)
unnamed: TP1.1, U1.10 (TINRUSH)
VDD: C1.1, C2.1, C3.1, C4.1, C5.1, C6.1, C7.1, C8.1, J1.1, J2.1, J3.1, J4.1, U1.5 (VM), U2.1 (VIN), U2.3 (ON/~OFF)

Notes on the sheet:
GAIN sel to ground has 205uA/A gain, allowing the max current
R2 converts current mirror to a voltage. Tieing the gain to ground means it is 205uA/A
VIPROPI (V) = IPROPI (A) x RIPROPI (Ω) Max of 2.05v on output w/3.3v VM. Needs 1.25v headroom to maintain accuracy. OCP is = (VVREF (V) / RIPROPI (Ω)) / AIPROPI (μA/A) In my case, that is 4.7 A
- tINRUSH = 6.5 x 10^6 x CINRUSH, to set inrush time - Current regulation Enabled at all times - Stall detection Enabled
JLC doesn't have these parts, and I need to add some custom processing to cut the 3569 parts in half, so not populated
JLC doesn't have the right version of the chip
Any capacitors on the power supply line should be rated above my intended voltage range of 3.7-7.4v The bulk capacitance on VM should also be really high
INPUT Chain
OUTPUT Chain

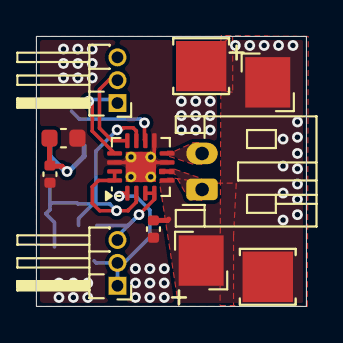
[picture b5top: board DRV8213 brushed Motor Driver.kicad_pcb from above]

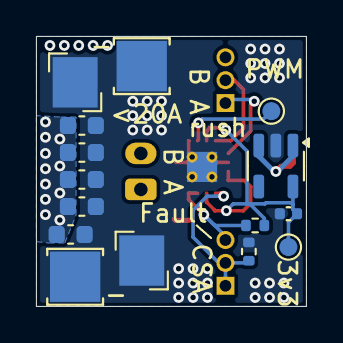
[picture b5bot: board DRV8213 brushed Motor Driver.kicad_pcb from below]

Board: 4 copper layers, 15.0 x 15.0 mm, 26 parts (15 on the bottom side), 10 nets.

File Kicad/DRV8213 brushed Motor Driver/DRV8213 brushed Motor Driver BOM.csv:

"Id";"Designator";"Footprint";"Quantity";"Designation";"Supplier and ref";
1;"J3,J2,J7,J6";"Keystone_3579";4;"Keystone 3579";;;
2;"J4,J1,J8,J5";"Keystone_3569_half";4;"Keystone 3569";;;
3;"C6,C8";"C_0402_1005Metric";2;"0.1uF, 16v";;;
4;"J11,J10";"PinHeader_1x03_P1.27mm_Horizontal";2;"1.27mm pin header";;;
5;"C7,C1,C4,C5,C3,C2";"C_0603_1608Metric";6;"10uF, 16v";;;
6;"J9";"JST_PH_S2B-PH-K_1x02_P2.00mm_Horizontal";1;"JST PH 2mm horizontal";;;
7;"U1";"WQFN-16-1EP_3x3mm_P0.5mm_EP1.68x1.68mm_ThermalVias";1;"DRV8213RTER";;;
8;"C9";"C_0402_1005Metric";1;"2.2uF, 10v";;;
9;"R2";"R_0402_1005Metric";1;"3.3k";;;
10;"U2";"SOT-23-5";1;"LP2981-3.3";;;
11;"R1";"R_0402_1005Metric";1;"10k";;;
